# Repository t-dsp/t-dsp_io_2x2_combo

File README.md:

# T-DSP IO 2x2 Combo

**Part of the [T-DSP](https://t-dsp.com) open modular audio platform.**

A 2-in / 2-out balanced audio I/O backplane for the [T-DSP TAC5212 Pro Audio Module](https://github.com/t-dsp/t-dsp_tac5212_pro_audio_module), with combo (XLR/TRS) inputs and XLR balanced outputs.

## About T-DSP

T-DSP is an open modular audio platform designed for musicians, engineers, and developers who want powerful digital signal processing in a flexible, hackable format. Built around the [Teensy](https://www.pjrc.com/teensy/) microcontroller and the [Teensy Audio Library](https://www.pjrc.com/teensy/td_libs_Audio.html), T-DSP combines studio-quality audio with a growing library of open-source modules for mixing, synthesis, effects, and more.

Learn more at [t-dsp.com](https://t-dsp.com).

## Overview

This board is a **backplane** -- a carrier PCB that hosts the TAC5212 Pro Audio Module and provides all the connectors and signal routing needed for a complete stereo audio interface. The TAC5212 module connects to this board via headers (removable) or straight pins (permanent), and handles codec, filtering, and power regulation. The DSP I/O header connects to a Teensy (or any I2S/I2C-compatible microcontroller) via ribbon cable. The T-DSP Desktop Pro provides 2 buffered expansion headers to interface up to 4 modules per port.

### Inputs
- **2x Neutrik NCJ6FA-H combo jacks** -- accept XLR (balanced) or 1/4" TRS (balanced/unbalanced)
- Suitable for line-level signals (consumer -10dBV or professional +4dBu)
### Outputs
- **2x Neutrik NC3MAH XLR male connectors** -- balanced output
- Suitable for line-level output to studio monitors, mixers, or other pro audio equipment

### Preamp Mezzanine Headers
- **2x 2x3 IDC headers (2.54mm pitch)** -- one per input channel, breaks out the differential input signal path
- Designed for mounting an external preamp module as a mezzanine board
- Solder bridge passes signal through by default -- cut the trace to insert a preamp

### Phantom Power Headers
- **2x JST XH 2-pin connectors** -- one per input channel, for connecting an external +48V phantom power supply. A switchable phantom power module is on the T-DSP roadmap.

## Documents

- [Schematic PDF](documentation/t-dsp_io_2x2_combo-schematic.pdf)
- [Schematic (KiCanvas)](https://kicanvas.org/?github=https://github.com/t-dsp/t-dsp_io_2x2_combo/blob/main/t-dsp_io_2x2_combo.kicad_sch)
- [PCB Layout (KiCanvas)](https://kicanvas.org/?github=https://github.com/t-dsp/t-dsp_io_2x2_combo/blob/main/t-dsp_io_2x2_combo.kicad_pcb)
- [3D Model (STL)](documentation/t-dsp_io_2x2_combo.stl)
- [Interactive BOM](https://t-dsp.github.io/t-dsp_io_2x2_combo/bom/ibom.html)

## Project Files

| Directory | Contents |
|-----------|----------|
| `/bom/` | [Interactive BOM](https://t-dsp.github.io/t-dsp_io_2x2_combo/bom/ibom.html) |
| `/documentation/` | [Schematic PDF](documentation/t-dsp_io_2x2_combo-schematic.pdf) |
| `/lib_fp/` | Custom KiCad footprint and symbol libraries |

## Dependencies

- **[T-DSP TAC5212 Pro Audio Module](https://github.com/t-dsp/t-dsp_tac5212_pro_audio_module)** -- the codec module that mounts onto this backplane
- **[KiCad](https://www.kicad.org/)** 9.0+ to open and edit the design files

## Status

This board has not yet been built. If you build one, we'd love to hear how it goes -- please open an issue or reach out with your findings.

## Related Projects

Browse all T-DSP modules and backplanes on the [T-DSP GitHub organization](https://github.com/orgs/t-dsp/repositories).

## Contact

For consulting, custom backplane design, or commercial licensing inquiries, reach out via [LinkedIn](https://linkedin.com/in/jayshoe).

## License

This project is licensed under the [Creative Commons Attribution-NonCommercial-ShareAlike 4.0 International (CC BY-NC-SA 4.0)](https://creativecommons.org/licenses/by-nc-sa/4.0/).

You are free to share and adapt this work for non-commercial purposes, as long as you give appropriate credit and distribute any derivatives under the same license.

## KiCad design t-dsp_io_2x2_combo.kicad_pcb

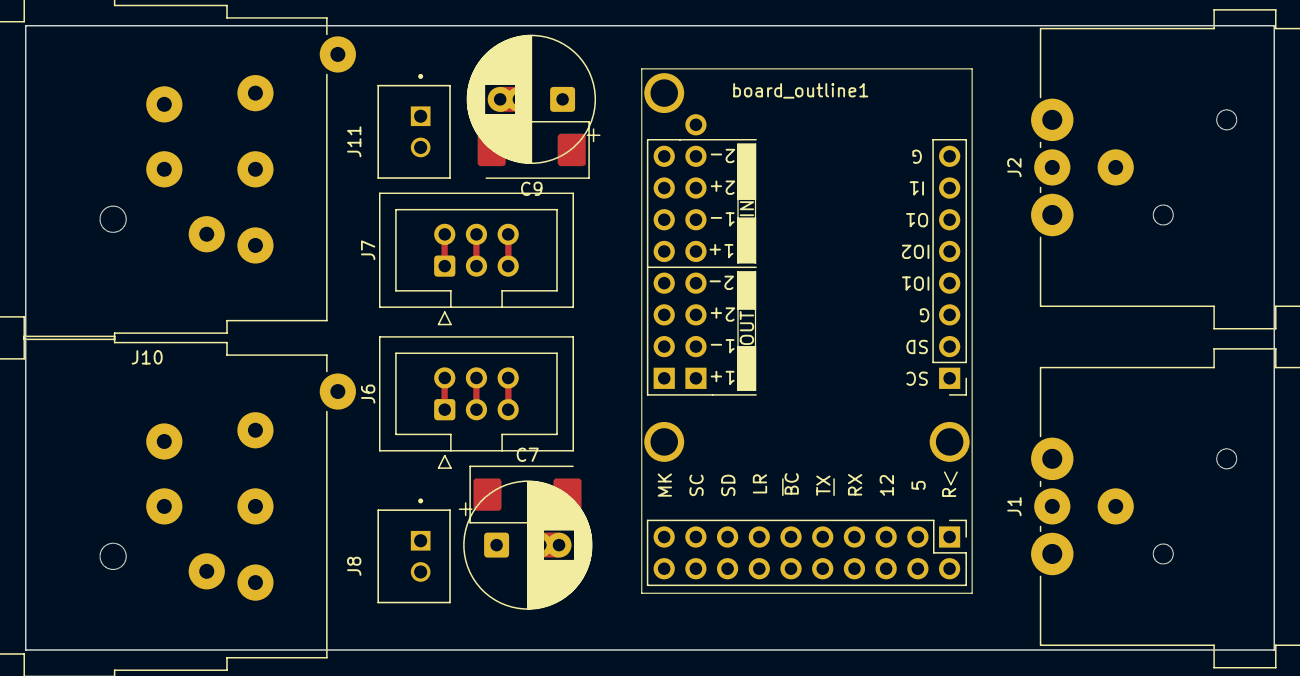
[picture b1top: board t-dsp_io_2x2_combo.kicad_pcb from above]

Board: 2 copper layers, 100.0 x 50.0 mm, 12 parts (0 on the bottom side), 6 nets, no tracks yet.

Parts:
C7, C9: 470 uF Electrolytic Audio-Grade; CP_Radial_D10.0mm_P5.00mm_AND_D8.0mm_P3.5mm
J1, J2: XLR3_Ground; XLRM_NC3MAH
J6, J7: Conn_02x03_Odd_Even; PREAMP_BYPASS_IDC-Header_2x03_P2.54mm_Vertical
J8, J11: B2B-XH-A; JST_B2B-XH-A
J9, J10: COMBO_NCJ6FA-H; COMBO_XLR_NCJ6FI-H
board_outline1: TAC5212 Module; audio_module_board_outline_50x34.5_d1_mod
board_outline3: board_outline; audio_project_board_outline_100x50_minus4mounts

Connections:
/AUDIO_IN1M: J6.5, board_outline1.31 (IN1M)
/AUDIO_IN1P: J6.1, board_outline1.29 (IN1P)
/AUDIO_IN2M: J7.5, board_outline1.35 (IN2M)
/AUDIO_IN2P: J7.1, board_outline1.33 (IN2P)
G: J6.3, J6.4, J7.3, J7.4
GND: board_outline1.6 (GNDD), board_outline1.8 (GNDD), board_outline1.10 (GNDD), board_outline1.12 (GNDD), board_outline1.14 (GNDD), board_outline1.16 (GNDD), board_outline1.18 (GNDD), board_outline1.20 (GNDD), board_outline1.22 (AGND), board_outline1.24 (AGND), board_outline1.26 (AGND), board_outline1.28 (AGND), board_outline1.30 (AGND), board_outline1.32 (AGND), board_outline1.34 (AGND), board_outline1.36 (AGND), board_outline1.51 (DGND)

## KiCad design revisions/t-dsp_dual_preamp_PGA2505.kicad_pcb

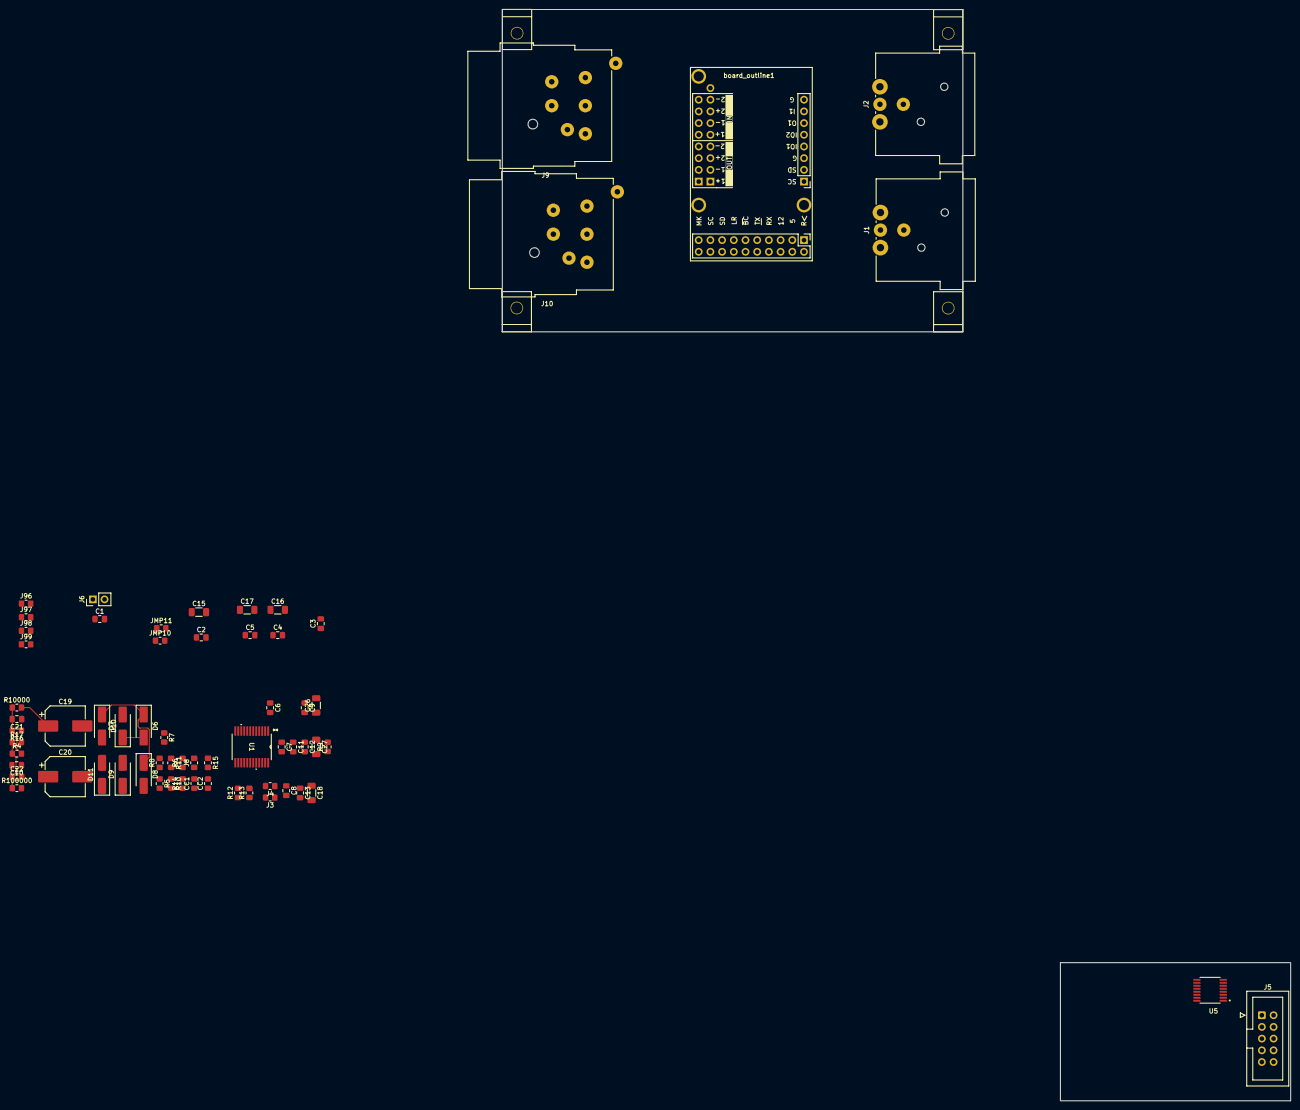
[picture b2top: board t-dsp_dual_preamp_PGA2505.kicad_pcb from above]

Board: 2 copper layers, 67 parts (0 on the bottom side), 38 nets.

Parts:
C1, C2, C3, C4, C5, C6, C7, C8, C9, C11, C12, C13: 0.1uF; C_0805_2012Metric_Pad1.18x1.45mm_HandSolder
C10, C21, C22: 1000pf; C_0805_2012Metric_Pad1.18x1.45mm_HandSolder
C15: 47uF; C_1206_3216Metric_Pad1.33x1.80mm_HandSolder
C16, C17, C18, C26, C27: 4.7uF; C_1206_3216Metric_Pad1.33x1.80mm_HandSolder
C19, C20: 47uF; CP_Elec_8x10.5
CC1, CC2: 0; R_0805_2012Metric_Pad1.20x1.40mm_HandSolder
D6, D7, D8, D9, D10: D_SMA_Handsoldering
D11: S1DB; D_SMA_Handsoldering
J1, J2: XLR3_Ground; XLRM_NC3MAH
J3, J4, J8: 0; R_0805_2012Metric_Pad1.20x1.40mm_HandSolder
J5: Conn_02x05_Odd_Even; IDC-Header_2x05_P2.54mm_Vertical
J6: Conn_01x02; PinHeader_1x02_P2.54mm_Vertical
J9, J10: COMBO_NCJ6FA-H; COMBO_XLR_NCJ6FI-H
J96, J97, J98, J99: 0 ohm; R_0805_2012Metric_Pad1.20x1.40mm_HandSolder
JMP10, JMP11: 0; R_0805_2012Metric_Pad1.20x1.40mm_HandSolder
R4: R_Small; R_0805_2012Metric_Pad1.20x1.40mm_HandSolder
R5, R6: N/C; R_0805_2012Metric_Pad1.20x1.40mm_HandSolder
R7, R8, R9, R10000, R100000: 10; R_0805_2012Metric_Pad1.20x1.40mm_HandSolder
R10, R11, R14, R15: 0; R_0805_2012Metric_Pad1.20x1.40mm_HandSolder
R12, R13: 0 ohm; R_0805_2012Metric_Pad1.20x1.40mm_HandSolder
R16, R17: 6.81k; R_0805_2012Metric_Pad1.20x1.40mm_HandSolder
U1: PGA2505IDB
U5: SC18IS606PWJ; SC18IS606PWJ_SOP65P640X110-16N
board_outline1: TAC5212 Module; audio_module_board_outline_50x34.5_d1_mod
board_outline2: board_outline; audio_project_board_outline_50x30
board_outline3: board_outline; audio_project_board_outline_100x70

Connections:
+5VA: D6.1 (K), D8.1 (K), D10.1 (K)
+12V: J5.1, J5.3
+48V: J5.9, J5.10
+48v: C1.1, J6.1, R16.1, R17.2
+VA: C5.2, C9.2, C17.1, C26.1, U1.16 (VA+)
-5VA: D7.2 (A), D9.2 (A), D11.2 (A)
-12V: J5.5, J5.7
-VA: C4.2, C11.2, C12.2, C16.2, C27.2, R9.1, U1.13 (VA-), U1.17 (VA-)
Earth: C3.1, C4.1, C5.1, C8.1, C9.1, C11.1, C12.1, C16.1, C17.2, C26.2, C27.1, D10.2 (A), D11.1 (K), J4.1, J8.1, JMP10.1, U1.1 (AGND)
G: J5.2, J5.4, J5.6, J5.8
GND: C2.2, C13.1, C15.2, C18.1, J96.1, J97.1, J98.1, J99.1, JMP10.2, JMP11.2, U1.7 (DGND), board_outline1.6 (GNDD), board_outline1.8 (GNDD), board_outline1.10 (GNDD), board_outline1.12 (GNDD), board_outline1.14 (GNDD), board_outline1.16 (GNDD), board_outline1.18 (GNDD), board_outline1.20 (GNDD), board_outline1.22 (AGND), board_outline1.24 (AGND), board_outline1.26 (AGND), board_outline1.28 (AGND), board_outline1.30 (AGND), board_outline1.32 (AGND), board_outline1.34 (AGND), board_outline1.36 (AGND), board_outline1.51 (DGND)
GNDPWR: C1.2, C3.2, C10.2, J6.2
unnamed: C10.1, C21.1, C22.2
unnamed: C19.1, R10000.2
unnamed: C19.2, R7.1
unnamed: C20.1, R100000.2
unnamed: C20.2, R8.1
unnamed: CC1.2, R14.2
unnamed: CC2.2, R15.1
unnamed: D6.2 (A), D7.1 (K), R7.2, R10.1
unnamed: D8.2 (A), D9.1 (K), R8.2, R11.1
unnamed: C8.2, J3.1
unnamed: J8.2, R5.1, R6.2
unnamed: R5.2, R10.2, R14.1
unnamed: R6.1, R11.2, R15.2
unnamed: C6.2, U1.21 (CS11)
unnamed: C6.1, U1.20 (CS12)
unnamed: C7.2, U1.19 (CS21)
unnamed: C7.1, U1.18 (CS22)
unnamed: J3.2, J4.2, U1.22 (VCOMIN)
unnamed: C13.2, C18.2, R9.2, U1.12 (VD-)
unnamed: CC1.1, U1.24 (VIN+)
unnamed: CC2.1, U1.23 (VIN-)
unnamed: R12.2, U1.15 (VOUT+)
unnamed: R13.2, U1.14 (VOUT-)
VCC: C2.1, C15.1
VIN1+: C21.2, R4.2, R16.2, R10000.1
VIN1-: C22.1, R4.1, R17.1, R100000.1

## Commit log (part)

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2026-02-08 Rename to t-dsp_io_2x2_combo and prepare for public release
    - Rename project files from t-dsp_dual_preamp to t-dsp_io_2x2_combo
    - Add README, LICENSE (CC BY-NC-SA 4.0), schematic PDF, interactive BOM
    - Add 3D render images for documentation
    - Remove third-party datasheets (docs/), old revisions, downloaded library ZIPs
    - Update .gitignore for clean repo
2026-02-08 Add KiCanvas links to README
2026-02-08 Add Related Projects section to README
2026-02-08 Add 3D STL model for GitHub viewer
